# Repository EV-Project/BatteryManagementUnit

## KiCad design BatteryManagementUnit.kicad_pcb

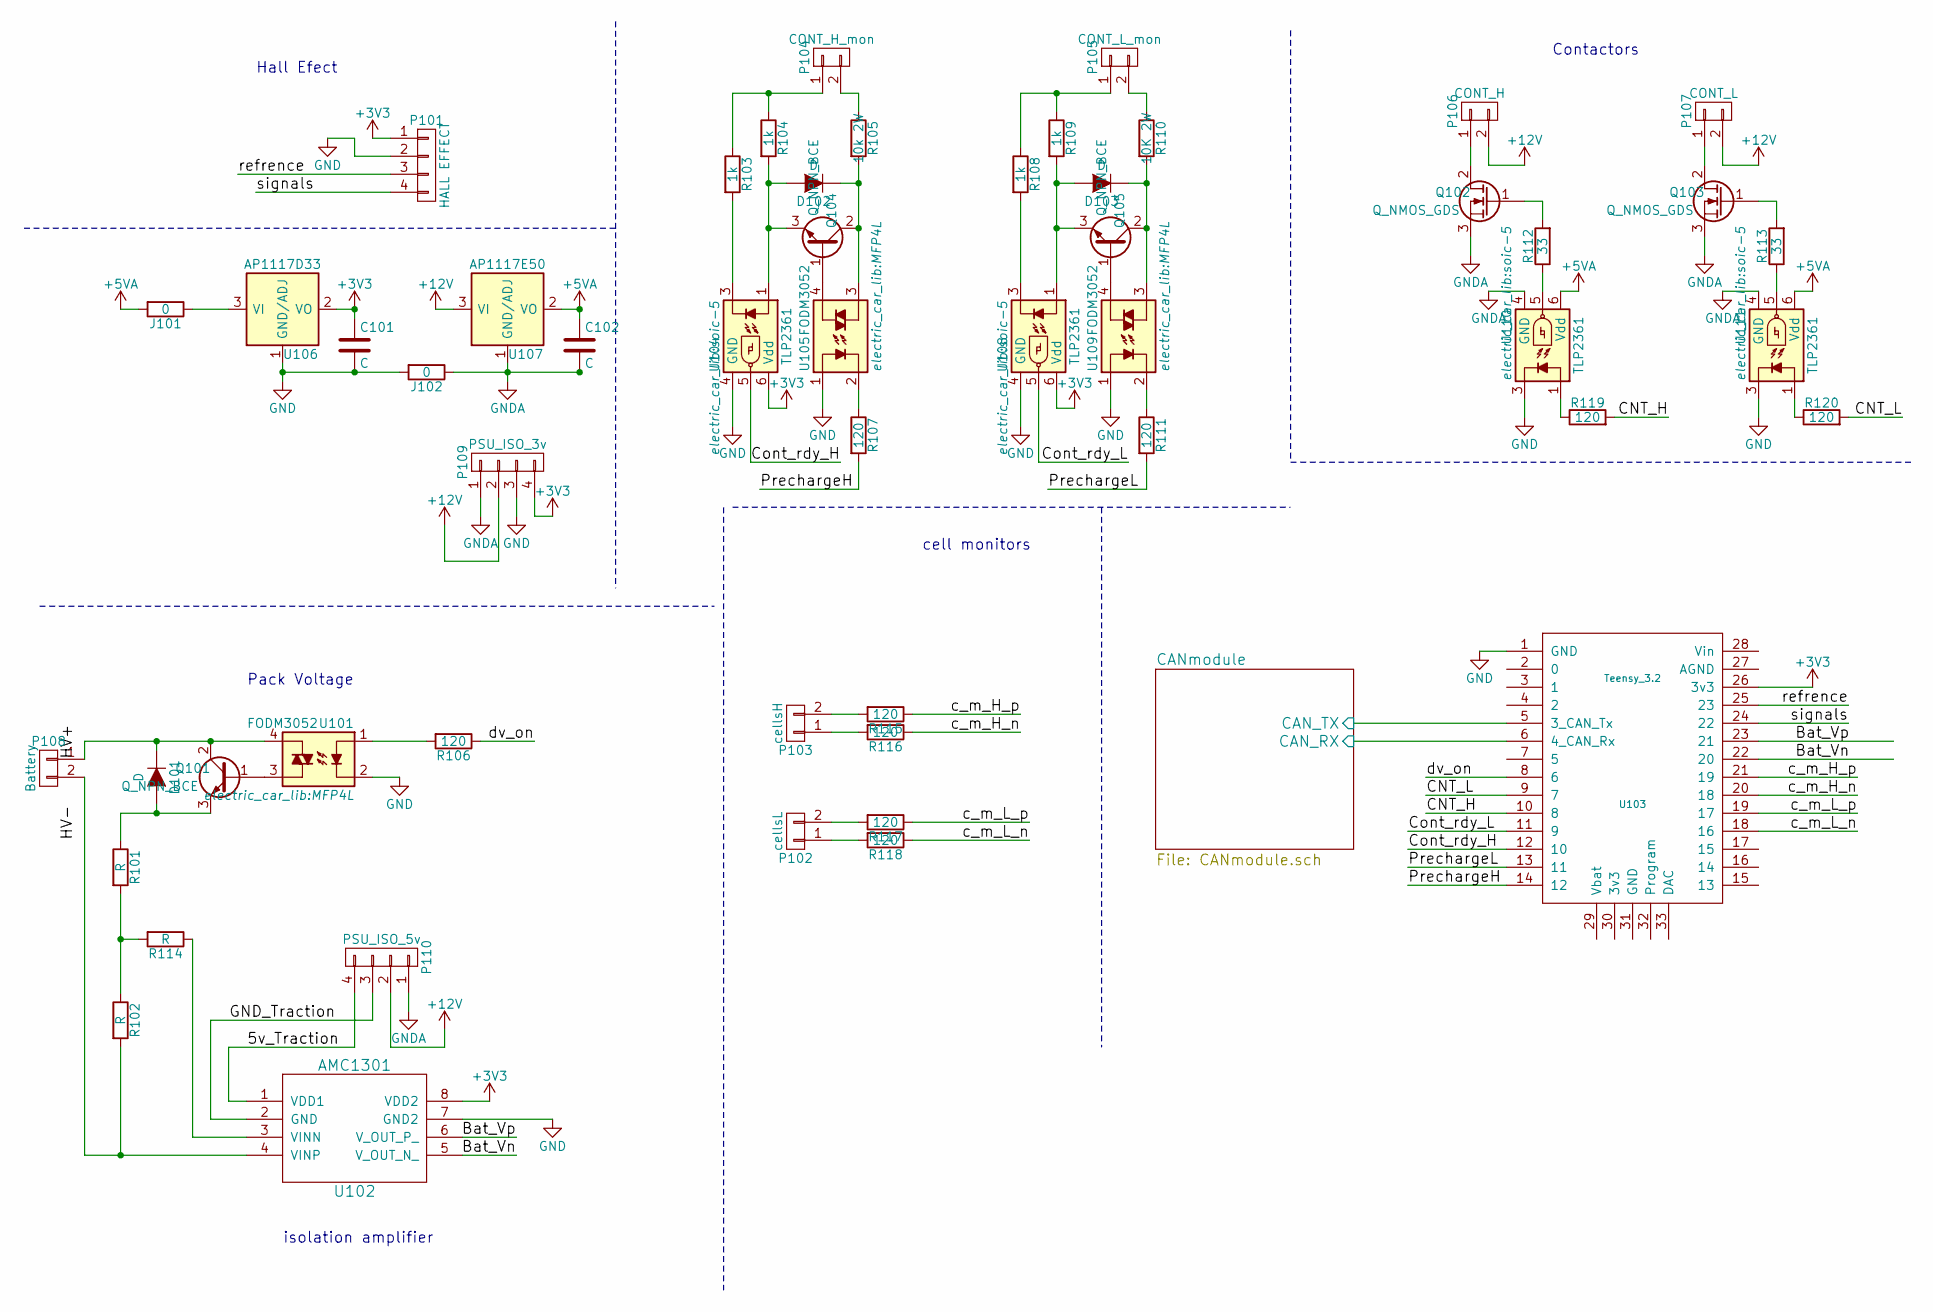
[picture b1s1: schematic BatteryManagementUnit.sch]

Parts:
C101, C102: C; C_1210_HandSoldering
D101, D102, D103: D; DO-214AB_Handsoldering
J101, J102: 0; R_1210_HandSoldering
P101: HALL EFFECT; Pin_Header_Straight_1x04
P102: cellsL; Pin_Header_Straight_1x02
P103: cellsH; Pin_Header_Straight_1x02
P104: CONT_H_mon; bornier2
P105: CONT_L_mon; bornier2
P106: CONT_H; bornier2
P107: CONT_L; bornier2
P108: Battery; bornier2
P109: PSU_ISO_3v; Pin_Header_Straight_1x04
P110: PSU_ISO_5v; Pin_Header_Straight_1x04
Q101, Q104, Q105: Q_NPN_BCE; TO-252-2Lead
Q102, Q103: Q_NMOS_GDS; TO-252-2Lead
R101, R102, R114: R; R_1206_HandSoldering
R103, R104, R108, R109: 1k; R_1206_HandSoldering
R105: 10k 2W; Resistor_Cement_KOA-BGR-3N
R106, R107, R111, R115, R116, R117, R118, R119, R120: 120; R_1206_HandSoldering
R110: 10K 2W; Resistor_Cement_KOA-BGR-3N
R112, R113: 33; R_1206_HandSoldering
U101, U105, U109: FODM3052; MFP4L
U102: AMC1301; amc1301
U103: Teensy_3.2; Teensy3.2
U104, U108, U110, U111: TLP2361; soic-5
U106: AP1117D33; SOT-223
U107: AP1117E50; SOT-223

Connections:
+3V3: C101.1, P101.1, P109.4, U102.8 (VDD2), U103.26 (3v3), U104.6 (Vdd), U106.2 (VO), U108.6 (Vdd); also elsewhere on the board
+5VA: C102.1, J101.2, U107.2 (VO), U110.6 (Vdd), U111.6 (Vdd); also elsewhere on the board
+12V: P106.2, P107.2, P109.2, P110.2, U107.3 (VI); also elsewhere on the board
/5v_Traction: P110.4, U102.1 (VDD1)
/Bat_Vn: U102.5 (V_OUT_N_), U103.22 (20)
/Bat_Vp: U102.6 (V_OUT_P_), U103.23 (21)
/CANmodule/CAN_RX: U103.6 (4_CAN_Rx); also elsewhere on the board
/CANmodule/CAN_TX: U103.5 (3_CAN_Tx); also elsewhere on the board
/CNT_H: R119.2, U103.10 (8)
/CNT_L: R120.2, U103.9 (7)
/Cont_rdy_H: U103.12 (10), U104.5
/Cont_rdy_L: U103.11 (9), U108.5
/GND_Traction: P110.3, U102.2 (GND)
/PrechargeH: R107.2, U103.14 (12)
/PrechargeL: R111.2, U103.13 (11)
/c_m_H_n: R116.1, U103.20 (18)
/c_m_H_p: R115.1, U103.21 (19)
/c_m_L_n: R118.1, U103.18 (16)
/c_m_L_p: R117.1, U103.19 (17)
/dv_on: R106.1, U103.8 (6)
/refrence: P101.3, U103.25 (23)
/signals: P101.4, U103.24 (22)
GND: C101.2, J102.2, P101.2, P109.3, U101.2, U102.7 (GND2), U103.1 (GND), U104.4 (GND), U105.1, U106.1 (GND/ADJ), U108.4 (GND), U109.1, U110.3, U111.3; also elsewhere on the board
GNDA: C102.2, J102.1, P109.1, P110.1, Q102.3 (S), Q103.3 (S), U107.1 (GND/ADJ), U110.4 (GND), U111.4 (GND); also elsewhere on the board
unnamed: D101.1 (K), P108.1, Q101.2 (C), U101.4
unnamed: D101.2 (A), Q101.3 (E), R101.1
unnamed: D102.1 (K), Q104.2 (C), R105.2, U105.3
unnamed: D102.2 (A), Q104.3 (E), R104.2, U104.1
unnamed: D103.1 (K), Q105.2 (C), R110.2, U109.3
unnamed: D103.2 (A), Q105.3 (E), R109.2, U108.1
unnamed: J101.1, U106.3 (VI)
unnamed: P102.1, R118.2
unnamed: P102.2, R117.2
unnamed: P103.1, R116.2
unnamed: P103.2, R115.2
unnamed: P104.1, R103.1, R104.1
unnamed: P104.2, R105.1
unnamed: P105.1, R108.1, R109.1
unnamed: P105.2, R110.1
unnamed: P106.1, Q102.2 (D)
unnamed: P107.1, Q103.2 (D)
unnamed: P108.2, R102.2, U102.4 (VINP)
unnamed: Q101.1 (B), U101.3
unnamed: Q102.1 (G), R112.2
unnamed: Q103.1 (G), R113.2
unnamed: Q104.1 (B), U105.4
unnamed: Q105.1 (B), U109.4
unnamed: R101.2, R102.1, R114.2
unnamed: R103.2, U104.3
unnamed: R106.2, U101.1
unnamed: R107.1, U105.2
unnamed: R108.2, U108.3
unnamed: R111.1, U109.2
unnamed: R112.1, U110.5
unnamed: R113.1, U111.5
unnamed: R114.1, U102.3 (VINN)
unnamed: R119.1, U110.1
unnamed: R120.1, U111.1

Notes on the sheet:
isolation amplifier
Contactors
Hall Efect
Pack Voltage
cell monitors

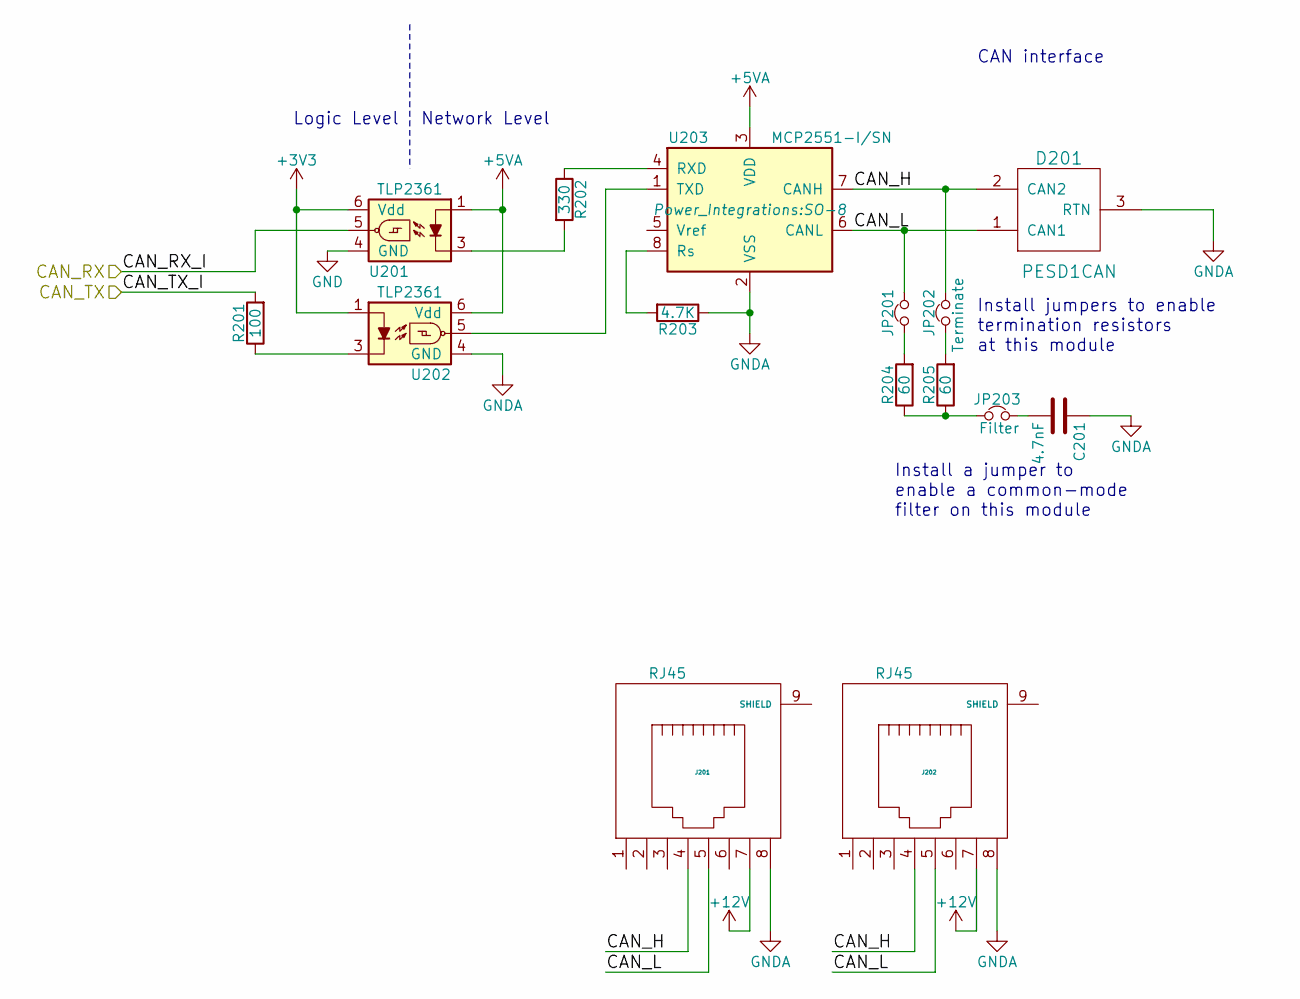
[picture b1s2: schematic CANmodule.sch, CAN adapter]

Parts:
C201: 4.7nF; C_1210_HandSoldering
D201: PESD1CAN; SOT-23_Handsoldering
J201, J202: RJ45; RJ45_8
JP201, JP202: Terminate; JumperSingle
JP203: Filter; JumperSingle
R201: 100; R_1206_HandSoldering
R202: 330; R_1206_HandSoldering
R203: 4.7K; R_1206_HandSoldering
R204, R205: 60; R_1206_HandSoldering
U201, U202: TLP2361; soic-5
U203: MCP2551-I/SN; SO-8

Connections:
+3V3: U201.6 (Vdd), U202.1; also elsewhere on the board
+5VA: U201.1, U202.6 (Vdd), U203.3 (VDD); also elsewhere on the board
+12V: J201.7, J202.7; also elsewhere on the board
/CANmodule/CAN_H: D201.2 (CAN2), J201.4, J202.4, JP202.1, U203.7 (CANH)
/CANmodule/CAN_L: D201.1 (CAN1), J201.5, J202.5, JP201.2, U203.6 (CANL)
/CANmodule/CAN_RX: U201.5; also elsewhere on the board
/CANmodule/CAN_TX: R201.2; also elsewhere on the board
GND: U201.4 (GND); also elsewhere on the board
GNDA: C201.1, D201.3 (RTN), J201.8, J202.8, R203.1, U202.4 (GND), U203.2 (VSS); also elsewhere on the board
unnamed: C201.2, JP203.2
unnamed: JP201.1, R204.2
unnamed: JP202.2, R205.2
unnamed: JP203.1, R204.1, R205.1
unnamed: R201.1, U202.3
unnamed: R202.1, U203.4 (RXD)
unnamed: R202.2, U201.3
unnamed: R203.2, U203.8 (Rs)
unnamed: U202.5, U203.1 (TXD)

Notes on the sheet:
Logic Level
Network Level
Install jumpers to enable termination resistors at this module
Install a jumper to enable a common-mode filter on this module
CAN interface

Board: 2 copper layers, 68 parts (0 on the bottom side), 69 nets, no tracks yet.

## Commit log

2016-10-25 triac hack
2016-11-15 partial layout
2016-11-15 completed schematic
2016-11-17 changed footprints, corrected psu, grouped parts
